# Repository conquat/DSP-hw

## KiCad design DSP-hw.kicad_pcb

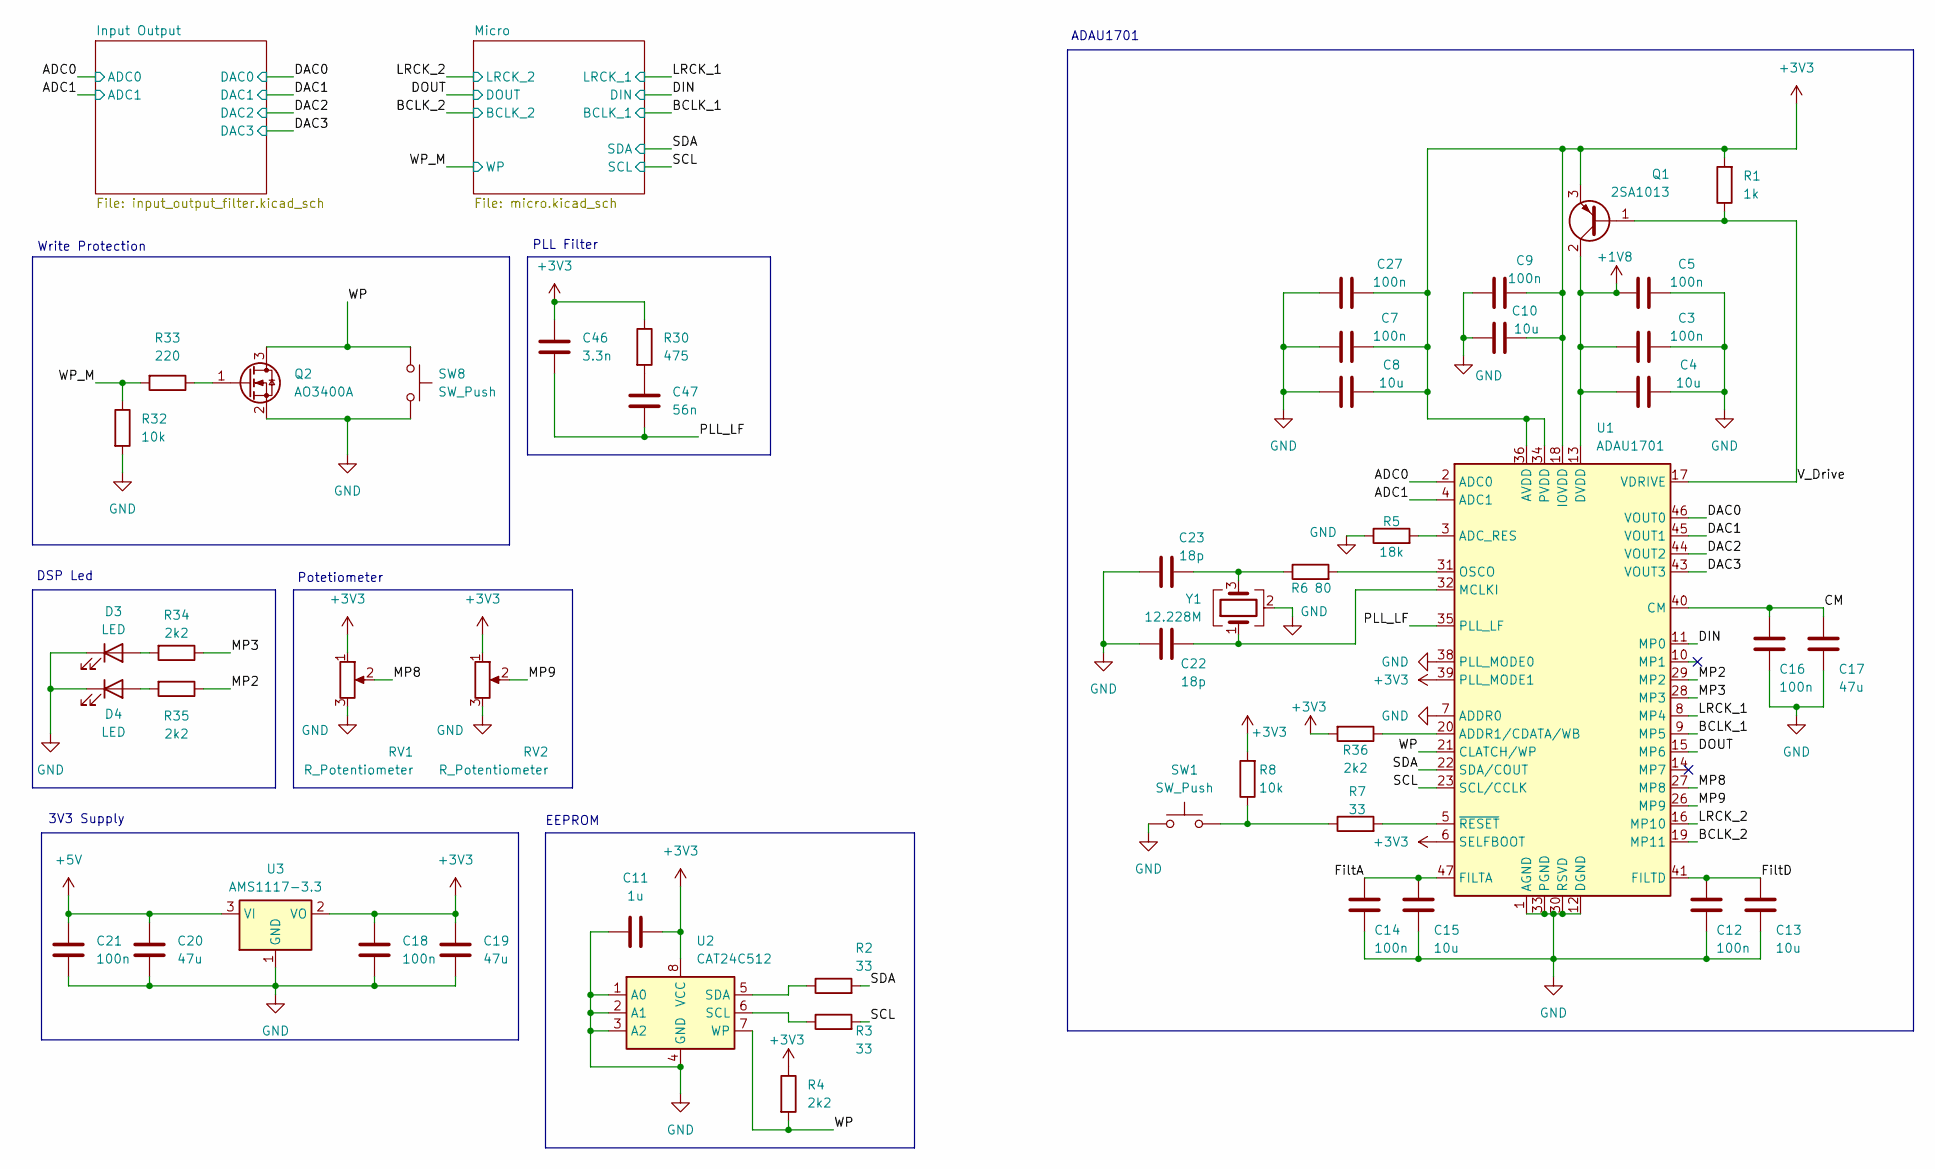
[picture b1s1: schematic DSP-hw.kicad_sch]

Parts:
C3, C5, C7, C9, C12, C14, C16, C18, C21, C27: 100n; C_0603_1608Metric
C4, C8, C10, C13, C15: 10u; C_0805_2012Metric
C11: 1u; C_0805_2012Metric
C17, C19, C20: 47u; C_Radial_D5.0mm_H11.0mm_P2.00mm
C22, C23: 18p; C_0603_1608Metric
C46: 3.3n; C_0603_1608Metric
C47: 56n; C_0603_1608Metric
D3, D4: LED; LED_1210_3225Metric
Q1: 2SA1013; SOT-89-3
Q2: AO3400A; SOT-23
R1: 1k; R_0603_1608Metric
R2, R3, R7: 33; R_0603_1608Metric
R4, R34, R35, R36: 2k2; R_0603_1608Metric
R5: 18k; R_0603_1608Metric
R6: 80; R_0603_1608Metric
R8, R32: 10k; R_0603_1608Metric
R30: 475; R_0603_1608Metric
R33: 220; R_0603_1608Metric
RV1, RV2: R_Potentiometer; Potentiometer_Alps_RK09Y11_Single_Horizontal
SW1, SW8: SW_Push; SW_SPST_PTS645Sx43SMTR92
U1: ADAU1701; LQFP-48_7x7mm_P0.5mm
U2: CAT24C512; SOIC-8_3.9x4.9mm_P1.27mm
U3: AMS1117-3.3; SOT-223-3_TabPin2
Y1: 12.228M; Crystal_SMD_3225-4Pin_3.2x2.5mm

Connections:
+1V8: C3.1, C4.1, C5.1, Q1.2 (C), U1.13 (DVDD), U1.24 (DVDD)
+3V3: C7.2, C8.2, C9.2, C10.2, C11.2, C18.1, C19.1, C27.2, C46.1, Q1.3 (E), R1.2, R4.1, R8.2, R30.1, R36.2, RV1.1, RV2.1, U1.6 (SELFBOOT), U1.18 (IOVDD), U1.34 (PVDD), U1.36 (AVDD), U1.39 (PLL_MODE1), U1.48 (AVDD), U2.8 (VCC), U3.2 (VO); also elsewhere on the board
+5V: C20.1, C21.1, U3.3 (VI); also elsewhere on the board
/ADC0: U1.2 (ADC0); also elsewhere on the board
/ADC1: U1.4 (ADC1); also elsewhere on the board
/BCLK_1: U1.9 (MP5); also elsewhere on the board
/BCLK_2: U1.19 (MP11); also elsewhere on the board
/CM: C16.1, C17.1, U1.40 (CM)
/DAC0: U1.46 (VOUT0); also elsewhere on the board
/DAC1: U1.45 (VOUT1); also elsewhere on the board
/DAC2: U1.44 (VOUT2); also elsewhere on the board
/DAC3: U1.43 (VOUT3); also elsewhere on the board
/DIN: U1.11 (MP0); also elsewhere on the board
/DOUT: U1.15 (MP6); also elsewhere on the board
/FiltA: C14.1, C15.1, U1.47 (FILTA)
/FiltD: C12.1, C13.1, U1.41 (FILTD)
/LRCK_1: U1.8 (MP4); also elsewhere on the board
/LRCK_2: U1.16 (MP10); also elsewhere on the board
/MP2: R35.1, U1.29 (MP2)
/MP3: R34.1, U1.28 (MP3)
/MP8: RV1.2, U1.27 (MP8)
/MP9: RV2.2, U1.26 (MP9)
/PLL_LF: C46.2, C47.2, U1.35 (PLL_LF)
/SCL: R3.2, U1.23 (SCL/CCLK); also elsewhere on the board
/SDA: R2.2, U1.22 (SDA/COUT); also elsewhere on the board
/V_Drive: Q1.1 (B), R1.1, U1.17 (VDRIVE)
/WP: Q2.3 (D), R4.2, SW8.1, U1.21 (CLATCH/WP), U2.7 (WP)
/WP_M: R32.1, R33.2; also elsewhere on the board
GND: C3.2, C4.2, C5.2, C7.1, C8.1, C9.1, C10.1, C11.1, C12.2, C13.2, C14.2, C15.2, C16.2, C17.2, C18.2, C19.2, C20.2, C21.2, C22.1, C23.1, C27.1, D3.1 (K), D4.1 (K), Q2.2 (S), R5.1, R32.2, RV1.3, RV2.3, SW1.1, SW8.2, U1.1 (AGND), U1.7 (ADDR0), U1.12 (DGND), U1.25 (DGND), U1.30 (RSVD), U1.33 (PGND), U1.37 (AGND), U1.38 (PLL_MODE0), U1.42 (AGND), U2.1 (A0), U2.2 (A1), U2.3 (A2), U2.4 (GND), U3.1 (GND), Y1.2 (G), Y1.4 (G); also elsewhere on the board
unnamed: C23.2, R6.1, Y1.3
unnamed: C47.1, R30.2
unnamed: D3.2 (A), R34.2
unnamed: D4.2 (A), R35.2
unnamed: Q2.1 (G), R33.1
unnamed: R7.1, R8.1, SW1.2
unnamed: R5.2, U1.3 (ADC_RES)
unnamed: R36.1, U1.20 (ADDR1/CDATA/WB)
unnamed: C22.2, U1.32 (MCLKI), Y1.1
unnamed: R6.2, U1.31 (OSCO)
unnamed: R7.2, U1.5 (~RESET)
unnamed: R3.1, U2.6 (SCL)
unnamed: R2.1, U2.5 (SDA)

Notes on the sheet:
3V3 Supply
ADAU1701
EEPROM
Write Protection
DSP Led
Potetiometer
PLL Filter

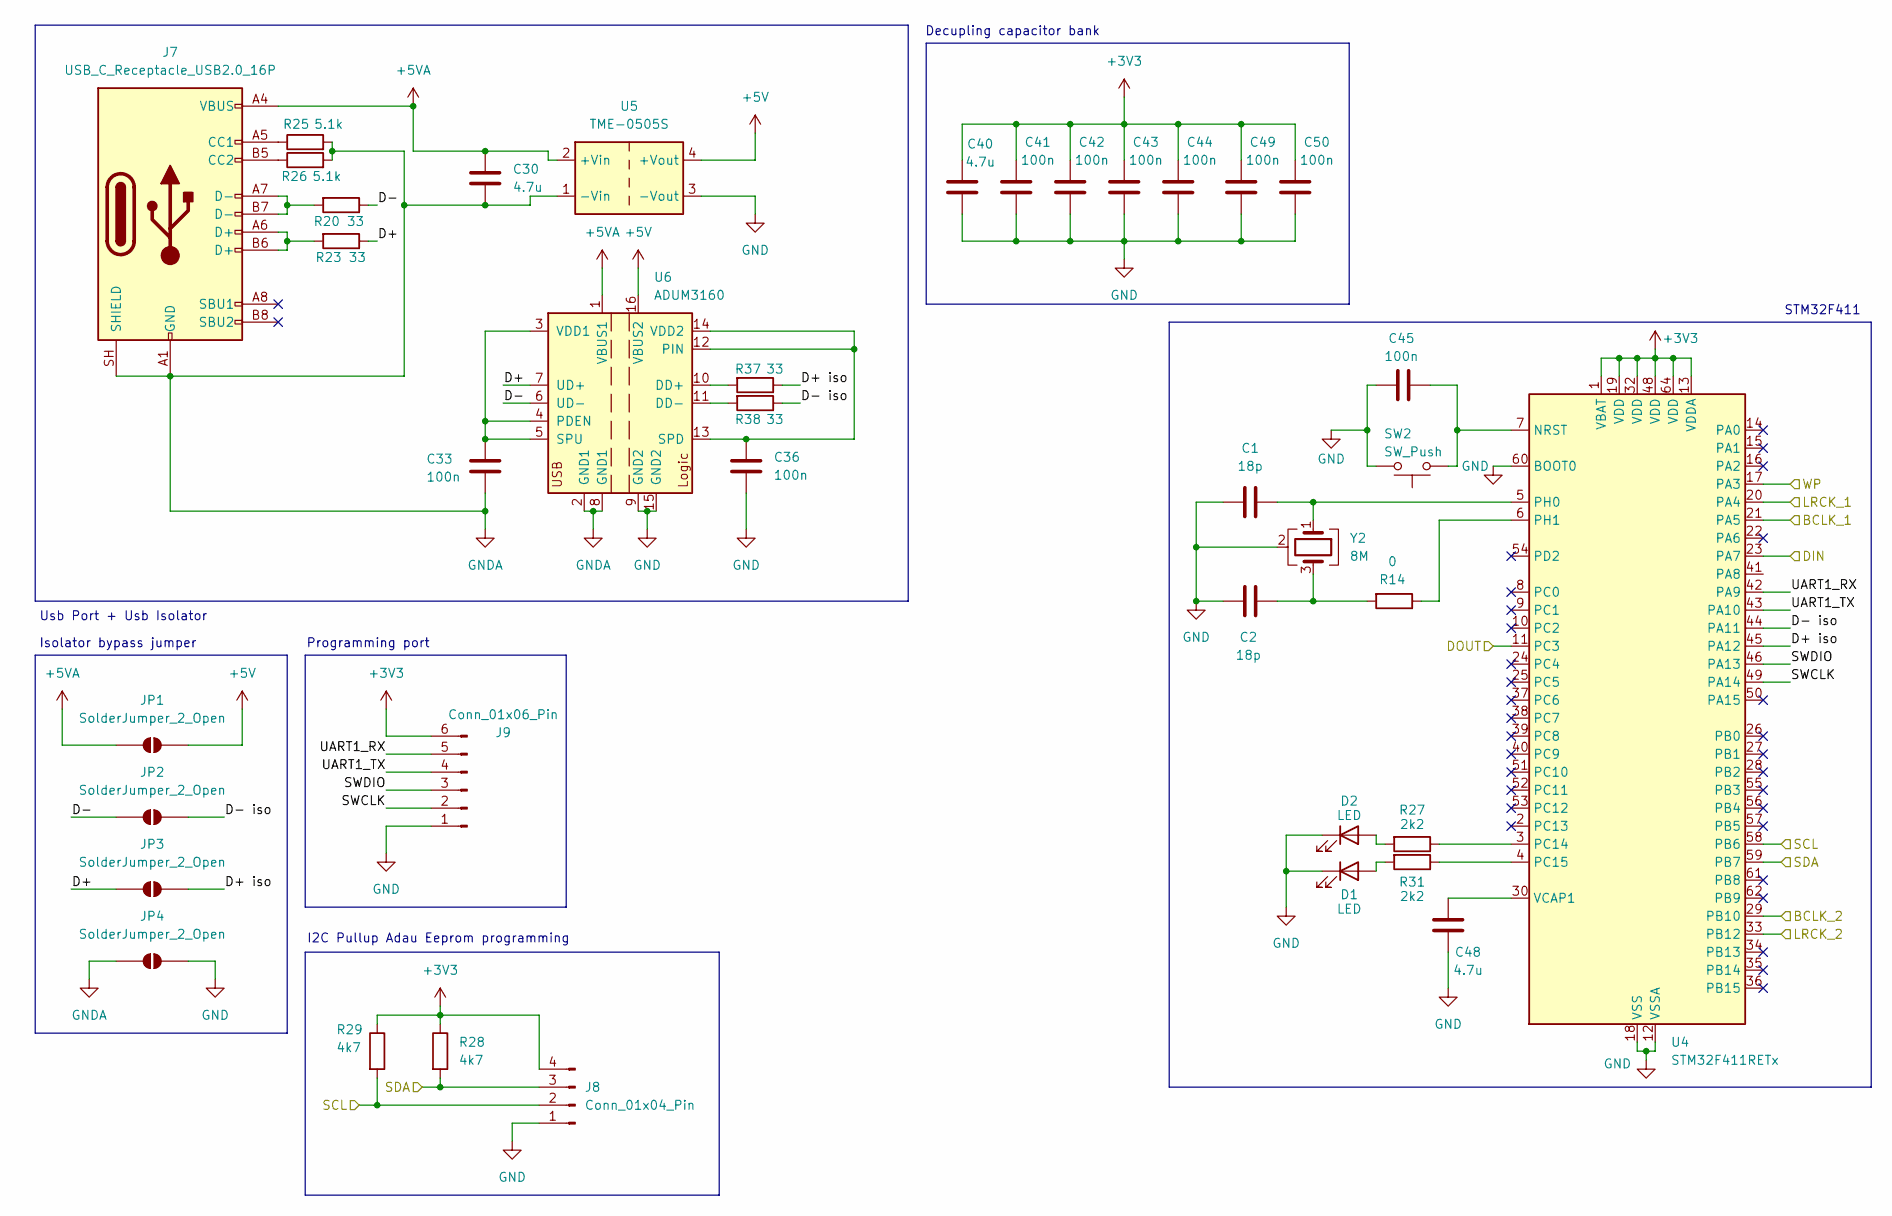
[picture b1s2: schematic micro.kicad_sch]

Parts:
C1, C2: 18p; C_0603_1608Metric
C30, C40, C48: 4.7u; C_Radial_D4.0mm_H7.0mm_P1.50mm
C33, C36, C41, C42, C43, C44, C45, C49, C50: 100n; C_0603_1608Metric
D1, D2: LED; LED_1210_3225Metric
J7: USB_C_Receptacle_USB2.0_16P; USB_C_Receptacle_GCT_USB4105-xx-A_16P_TopMnt_Horizontal
J8: Conn_01x04_Pin; JST_XH_B4B-XH-A_1x04_P2.50mm_Vertical
J9: Conn_01x06_Pin; JST_XH_B6B-XH-A_1x06_P2.50mm_Vertical
JP1, JP2, JP3, JP4: SolderJumper_2_Open; SolderJumper-2_P1.3mm_Open_TrianglePad1.0x1.5mm
R14: 0; R_0603_1608Metric
R20, R23, R37, R38: 33; R_0603_1608Metric
R25, R26: 5.1k; R_0603_1608Metric
R27, R31: 2k2; R_0603_1608Metric
R28, R29: 4k7; R_0603_1608Metric
SW2: SW_Push; SW_SPST_PTS645Sx43SMTR92
U4: STM32F411RETx; LQFP-64_10x10mm_P0.5mm
U5: TME-0505S; Converter_DCDC_TRACO_TME_03xxS_05xxS_12xxS_Single_THT
U6: ADUM3160; SOIC-16W_7.5x10.3mm_P1.27mm
Y2: 8M; Crystal_SMD_3225-4Pin_3.2x2.5mm

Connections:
+3V3: C40.1, C41.1, C42.1, C43.1, C44.1, C49.1, C50.1, J8.4, J9.6, R28.1, R29.1, U4.1 (VBAT), U4.13 (VDDA), U4.19 (VDD), U4.32 (VDD), U4.48 (VDD), U4.64 (VDD); also elsewhere on the board
+5V: JP1.2 (B), U5.4 (+Vout), U6.16 (VBUS2); also elsewhere on the board
+5VA: C30.1, J7.A4 (VBUS), J7.A9 (VBUS), J7.B4 (VBUS), J7.B9 (VBUS), JP1.1 (A), U5.2 (+Vin), U6.1 (VBUS1)
/BCLK_1: U4.21 (PA5); also elsewhere on the board
/BCLK_2: U4.29 (PB10); also elsewhere on the board
/DIN: U4.23 (PA7); also elsewhere on the board
/DOUT: U4.11 (PC3); also elsewhere on the board
/LRCK_1: U4.20 (PA4); also elsewhere on the board
/LRCK_2: U4.33 (PB12); also elsewhere on the board
/Micro/D+: JP3.1 (A), R23.1, U6.7 (UD+)
/Micro/D+ iso: JP3.2 (B), R37.1, U4.45 (PA12)
/Micro/D-: JP2.1 (A), R20.1, U6.6 (UD-)
/Micro/D- iso: JP2.2 (B), R38.1, U4.44 (PA11)
/Micro/SWCLK: J9.2, U4.49 (PA14)
/Micro/SWDIO: J9.3, U4.46 (PA13)
/Micro/UART1_RX: J9.5, U4.42 (PA9)
/Micro/UART1_TX: J9.4, U4.43 (PA10)
/SCL: J8.2, R29.2, U4.58 (PB6); also elsewhere on the board
/SDA: J8.3, R28.2, U4.59 (PB7); also elsewhere on the board
/WP_M: U4.17 (PA3); also elsewhere on the board
GND: C1.1, C2.1, C36.2, C40.2, C41.2, C42.2, C43.2, C44.2, C45.2, C48.2, C49.2, C50.2, D1.1 (K), D2.1 (K), J8.1, J9.1, JP4.2 (B), SW2.2, U4.12 (VSSA), U4.18 (VSS), U4.31 (VSS), U4.47 (VSS), U4.60 (BOOT0), U4.63 (VSS), U5.3 (-Vout), U6.9 (GND2), U6.15 (GND2), Y2.2 (G), Y2.4 (G); also elsewhere on the board
GNDA: C30.2, C33.2, J7.A1 (GND), J7.A12 (GND), J7.B1 (GND), J7.B12 (GND), J7.SH (SHIELD), JP4.1 (A), R25.2, R26.2, U5.1 (-Vin), U6.2 (GND1), U6.8 (GND1)
unnamed: C2.2, R14.2, Y2.3
unnamed: D1.2 (A), R31.2
unnamed: D2.2 (A), R27.2
unnamed: J7.A5 (CC1), R25.1
unnamed: J7.B5 (CC2), R26.1
unnamed: J7.A6 (D+), J7.B6 (D+), R23.2
unnamed: J7.A7 (D-), J7.B7 (D-), R20.2
unnamed: C45.1, SW2.1, U4.7 (NRST)
unnamed: R27.1, U4.3 (PC14)
unnamed: R31.1, U4.4 (PC15)
unnamed: C1.2, U4.5 (PH0), Y2.1
unnamed: R14.1, U4.6 (PH1)
unnamed: C48.1, U4.30 (VCAP1)
unnamed: R37.2, U6.10 (DD+)
unnamed: R38.2, U6.11 (DD-)
unnamed: C33.1, U6.3 (VDD1), U6.4 (PDEN), U6.5 (SPU)
unnamed: C36.1, U6.12 (PIN), U6.13 (SPD), U6.14 (VDD2)

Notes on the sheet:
STM32F411
Usb Port + Usb Isolator
Programming port
I2C Pullup Adau Eeprom programming
Isolator bypass jumper
Decupling capacitor bank

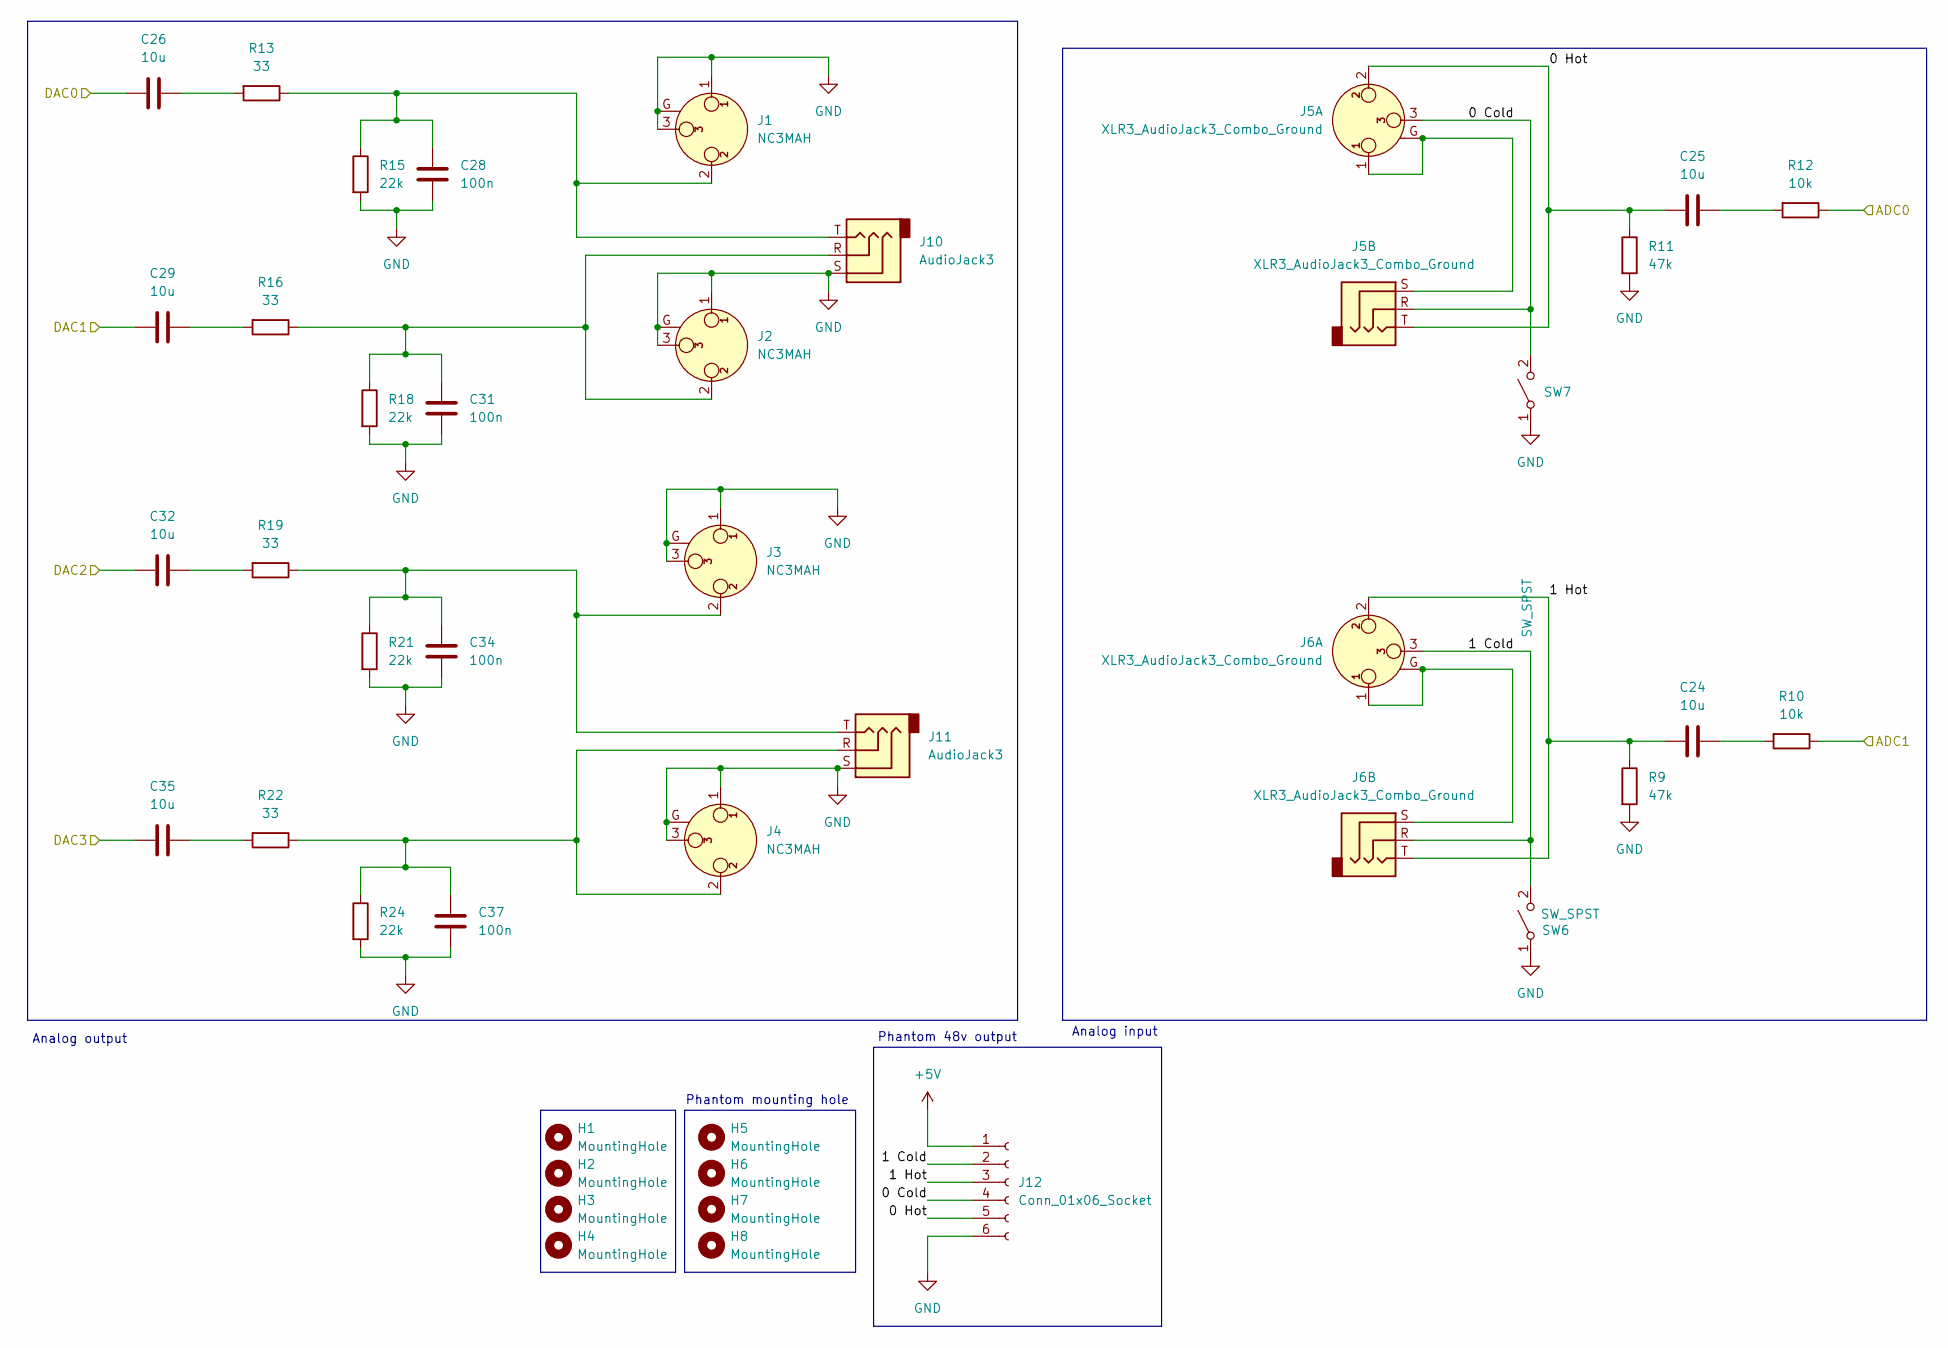
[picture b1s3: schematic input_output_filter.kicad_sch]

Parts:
C24, C25, C26, C29, C32, C35: 10u; C_0805_2012Metric
C28, C31, C34, C37: 100n; C_0603_1608Metric
H1, H2, H3, H4: MountingHole; MountingHole_3.2mm_M3_Pad_Via
H5, H6, H7, H8: MountingHole; MountingHole_2.2mm_M2_Pad_Via
J1, J2, J3, J4: NC3MAH; Jack_XLR_Neutrik_NC3MAH_Horizontal
J5, J6: XLR3_AudioJack3_Combo_Ground; Jack_XLR-6.35mm_Neutrik_NCJ6FA-H-0_Horizontal
J10, J11: AudioJack3; Jack_3.5mm_CUI_SJ1-3523N_Horizontal
J12: Conn_01x06_Socket; PinHeader_1x06_P2.54mm_Vertical
R9, R11: 47k; R_0603_1608Metric
R10, R12: 10k; R_0603_1608Metric
R13, R16, R19, R22: 33; R_0603_1608Metric
R15, R18, R21, R24: 22k; R_0603_1608Metric
SW6, SW7: SW_SPST; SW_DIP_SPSTx01_Slide_9.78x4.72mm_W7.62mm_P2.54mm

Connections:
+5V: J12.1; also elsewhere on the board
/ADC0: R12.1; also elsewhere on the board
/ADC1: R10.1; also elsewhere on the board
/DAC0: C26.1; also elsewhere on the board
/DAC1: C29.1; also elsewhere on the board
/DAC2: C32.1; also elsewhere on the board
/DAC3: C35.1; also elsewhere on the board
/Input Output/0 Cold: J5.3, J5.R, J12.4, SW7.2 (B)
/Input Output/0 Hot: C25.1, J5.2, J5.T, J12.5, R11.1
/Input Output/1 Cold: J6.3, J6.R, J12.2, SW6.2 (B)
/Input Output/1 Hot: C24.1, J6.2, J6.T, J12.3, R9.1
GND: C28.2, C31.2, C34.2, C37.2, J1.1, J1.3, J1.G, J2.1, J2.3, J2.G, J3.1, J3.3, J3.G, J4.1, J4.3, J4.G, J10.S, J11.S, J12.6, R9.2, R11.2, R15.2, R18.2, R21.2, R24.2, SW6.1 (A), SW7.1 (A); also elsewhere on the board
unnamed: C24.2, R10.2
unnamed: C25.2, R12.2
unnamed: C26.2, R13.2
unnamed: C28.1, J1.2, J10.T, R13.1, R15.1
unnamed: C29.2, R16.2
unnamed: C31.1, J2.2, J10.R, R16.1, R18.1
unnamed: C32.2, R19.2
unnamed: C34.1, J3.2, J11.T, R19.1, R21.1
unnamed: C35.2, R22.2
unnamed: C37.1, J4.2, J11.R, R22.1, R24.1
unnamed: J5.1, J5.G, J5.S
unnamed: J6.1, J6.G, J6.S

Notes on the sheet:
Phantom 48v output
Phantom mounting hole
Analog output
Analog input

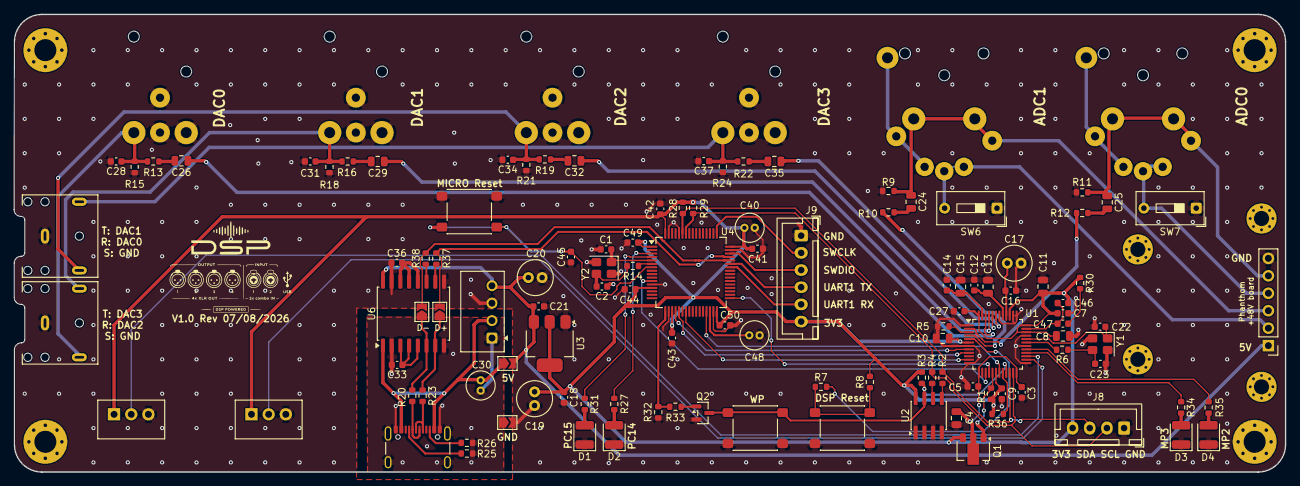
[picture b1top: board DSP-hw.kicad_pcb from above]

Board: 2 copper layers, 185.0 x 66.6 mm, 129 parts (0 on the bottom side), 85 nets.

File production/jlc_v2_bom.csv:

Designator,Footprint,Quantity,Value,LCSC Part #
"C10, C13, C15, C17, C4, C8",0805,6,10u,
C11,0805,1,1u,
"C12, C14, C16, C18, C21, C28, C3, C31, C33, C34, C36, C37, C41, C42, C43, C44, C45, C9",0603,18,100n,
"C19, C20",C_Radial_D5.0mm_H11.0mm_P2.00mm,2,47u,
"C22, C23",0603,2,22p,
"C24, C25, C26, C29, C32, C35",1210,6,10u,
"C30, C40",C_Radial_D4.0mm_H7.0mm_P1.50mm,2,4.7u,
C46,0603,1,3.3n,
C47,0603,1,56n,
C48,0603,1,4.7u,
C7,0603,1,1u,
"D1, D2, D3, D4",1210,4,LED,
"J1, J2, J3, J4",Jack_XLR_Neutrik_NC3MAH_Horizontal,4,NC3MAH,
"J10, J11",Jack_3.5mm_Lumberg_1503_07_Horizontal,2,AudioJack3,
"J5, J6",Jack_XLR-6.35mm_Neutrik_NCJ6FA-H-0_Horizontal,2,XLR3_AudioJack3_Combo_Ground,
J7,USB_C_Receptacle_GCT_USB4105-xx-A_16P_TopMnt_Horizontal,1,USB_C_Receptacle_USB2.0_16P,
J8,JST_XH_B4B-XH-AM_1x04_P2.50mm_Vertical,1,Conn_01x04_Pin,
J9,JST_XH_B6B-XH-A_1x06_P2.50mm_Vertical,1,Conn_01x06_Pin,
Q1,TO-92_Inline,1,BC327,
Q2,SOT-23,1,AO3400A,
R1,0603,1,1k,
"R10, R12, R32, R8",0603,4,10k,
"R11, R9",0603,2,47k,
"R13, R16, R19, R2, R22, R3, R7",0603,7,33,
"R15, R18, R21, R24",0603,4,22k,
"R25, R26",0603,2,5.1k,
"R27, R31, R34, R35, R4",0603,5,2k2,
"R28, R29",0603,2,4k7,
R30,0603,1,475,
R33,0603,1,220,
R5,0603,1,18k,
R6,0603,1,100,
"RV1, RV2",Potentiometer_Alps_RK09Y11_Single_Horizontal,2,R_Potentiometer,
"SW1, SW2, SW8",SW_SPST_PTS645Sx43SMTR92,3,SW_Push,
"SW6, SW7",SW_DIP_SPSTx01_Slide_9.78x4.72mm_W7.62mm_P2.54mm,2,SW_SPST,
U1,LQFP-48_7x7mm_P0.5mm,1,ADAU1701,
U2,SOIC-8_3.9x4.9mm_P1.27mm,1,CAT24C256,
U3,SOT-223-3_TabPin2,1,AMS1117-3.3,
U4,LQFP-64_10x10mm_P0.5mm,1,STM32F411RETx,
U5,Converter_DCDC_TRACO_TME_03xxS_05xxS_12xxS_Single_THT,1,TME-0505S,
U6,SOIC-16W_7.5x10.3mm_P1.27mm,1,ADUM3160,
Y1,Crystal_SMD_HC49-SD,1,12.228M,
